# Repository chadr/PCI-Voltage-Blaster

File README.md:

# PCI Voltage Blaster
 PCI +3.3V version of the Voltage Blaster project. This is meant to power PCI cards keyed for +5V slots that still require +3.3V. Like the "new" Chinese made ATI Rage XL PCI cards found all over eBay.

 This mini version is good for about 500mA. It's not meant for high-powered PCI devices.

 NOTE: Most +5V only PCI motherboards don't route the +3.3V pins between slots. You will have to add bodge wires on the back of your motherboard between the slot with the Voltage Blaster and the slot that needs +3.3V.

## Getting Boards Made
Either JLCPCB or PCBWay do a decent job. Your choice for HASL or ENIG. Doesn't really matter here. Choose 1.6mm board thickness.

**Bill of Materials**
**Item**|**Qty**|**MFG Part Num**
:-----:|:-----:|:-----:
+3.3V LDO|1|AMS1117-3.3 (DPAK)
10uF 16V Axial Electrolytic Capacitor|2|Nichicon VX Series
5mm LED Diffused|1|Any Generic Red or Green 5mm LED
120R 1/8 Watt Metal Film Resistor 1%|1|Any
Schottky Diode 40 Volt 1.0 Amp|1|SB140-E3/73

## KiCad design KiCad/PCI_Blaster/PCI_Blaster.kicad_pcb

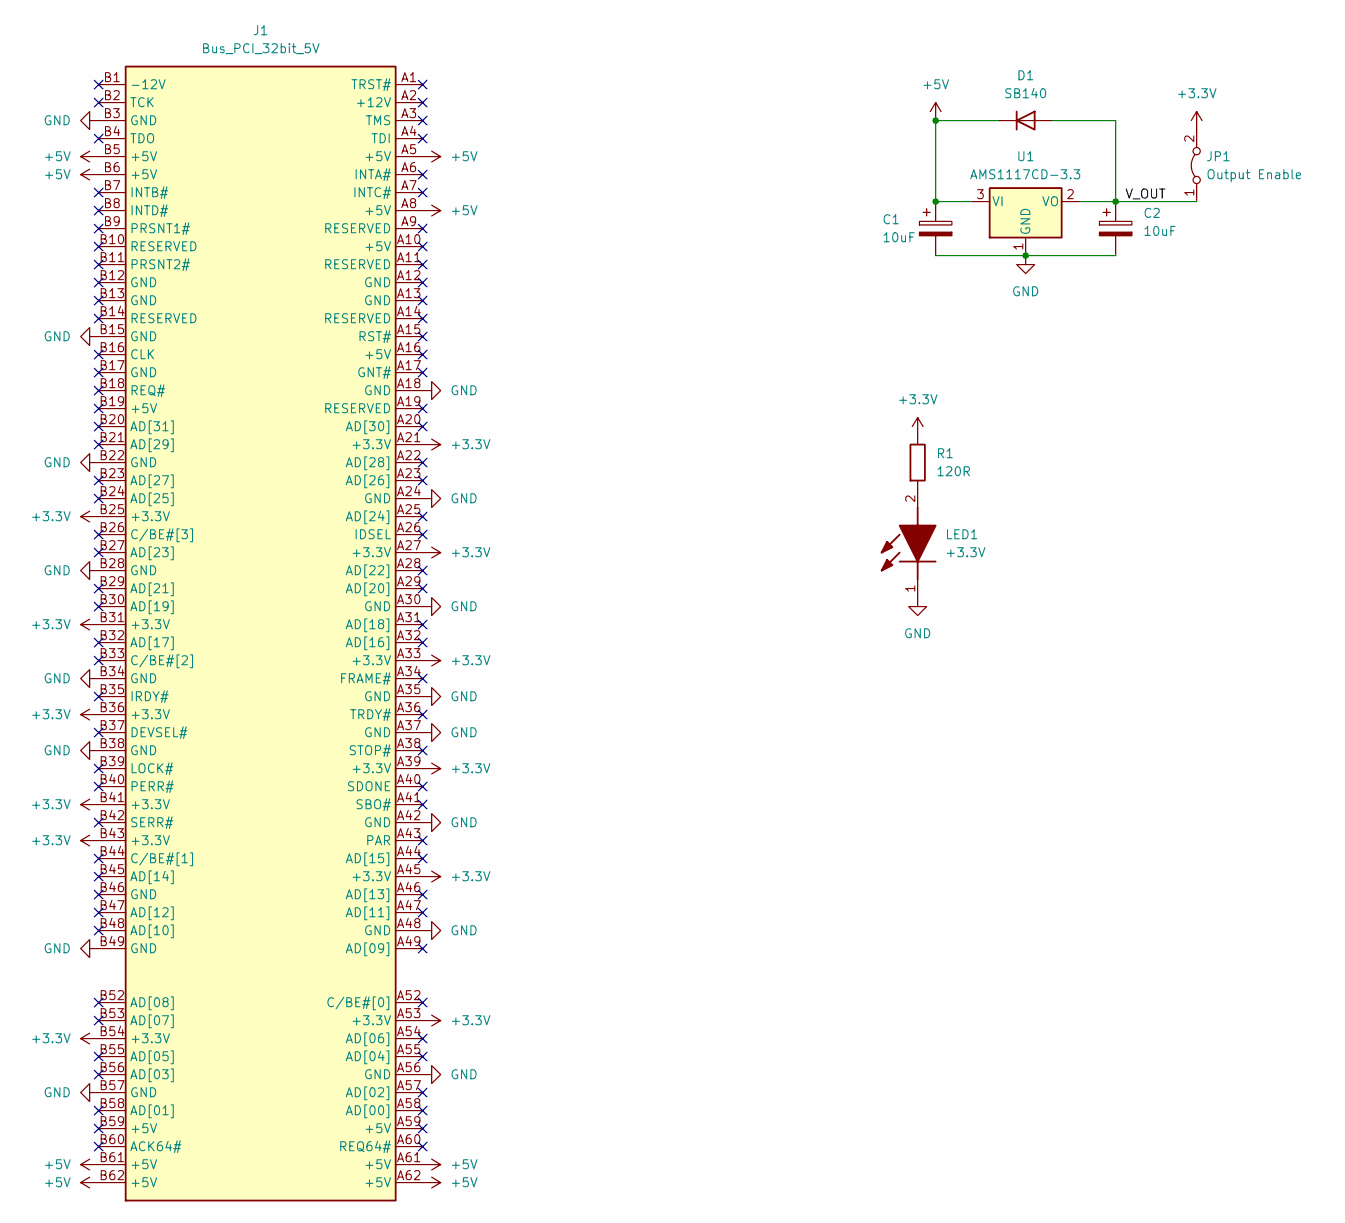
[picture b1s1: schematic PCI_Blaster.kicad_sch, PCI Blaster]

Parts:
C1, C2: 10uF; C_Axial_L5.1mm_D3.1mm_P10.00mm_Horizontal
D1: SB140; D_DO-41_SOD81_P7.62mm_Horizontal
J1: Bus_PCI_32bit_5V; BUS_PCI
JP1: Output Enable; PinHeader_1x02_P2.54mm_Vertical
LED1: +3.3V; LED_D3.0mm; Manufacturer_Part_Number LTL-4231NHBP; Mouser Part Number 859-LTL-4231NHBP
R1: 120R; R_Axial_DIN0204_L3.6mm_D1.6mm_P5.08mm_Horizontal
U1: AMS1117CD-3.3; TO-252-2

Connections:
+3.3V: J1.A21 (+3.3V), J1.A27 (+3.3V), J1.A33 (+3.3V), J1.A39 (+3.3V), J1.A45 (+3.3V), J1.A53 (+3.3V), J1.B25 (+3.3V), J1.B31 (+3.3V), J1.B36 (+3.3V), J1.B41 (+3.3V), J1.B43 (+3.3V), J1.B54 (+3.3V), JP1.2 (B), R1.1
+5V: C1.1, D1.1 (K), J1.A5 (+5V), J1.A8 (+5V), J1.A61 (+5V), J1.A62 (+5V), J1.B5 (+5V), J1.B6 (+5V), J1.B61 (+5V), J1.B62 (+5V), U1.3 (VI)
/V_OUT: C2.1, D1.2 (A), JP1.1 (A), U1.2 (VO)
GND: C1.2, C2.2, J1.A18 (GND), J1.A24 (GND), J1.A30 (GND), J1.A35 (GND), J1.A37 (GND), J1.A42 (GND), J1.A48 (GND), J1.A56 (GND), J1.B3 (GND), J1.B15 (GND), J1.B22 (GND), J1.B28 (GND), J1.B34 (GND), J1.B38 (GND), J1.B49 (GND), J1.B57 (GND), LED1.1 (K), U1.1 (GND)
unnamed: LED1.2 (A), R1.2

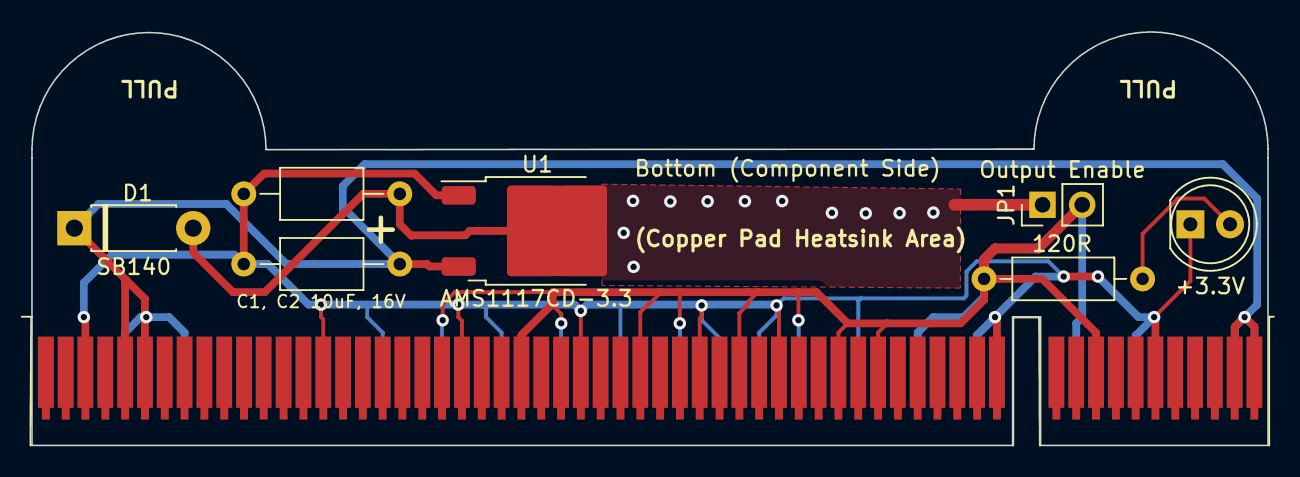
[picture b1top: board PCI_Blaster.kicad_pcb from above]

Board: 2 copper layers, 79.2 x 26.5 mm, 8 parts (0 on the bottom side), 5 nets.

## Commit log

2023-11-03 add panels
2024-01-09 redo pcb layout
2024-01-09 add images
2024-03-12 update images and docs
